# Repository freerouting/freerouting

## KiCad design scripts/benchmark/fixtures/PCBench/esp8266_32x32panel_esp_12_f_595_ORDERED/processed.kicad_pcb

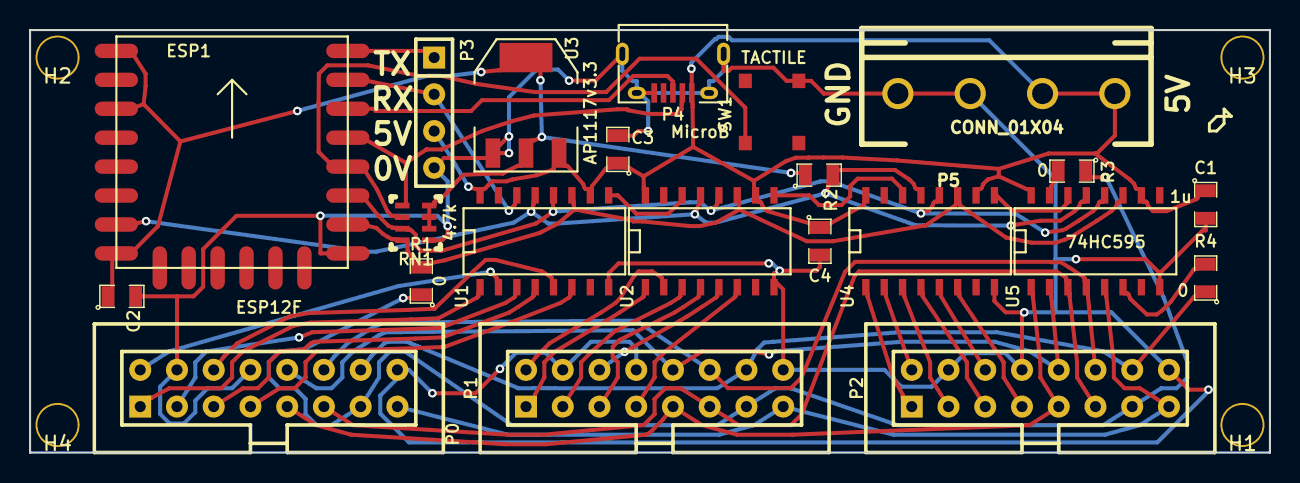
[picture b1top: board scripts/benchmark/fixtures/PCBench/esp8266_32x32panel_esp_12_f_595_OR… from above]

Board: 2 copper layers, 85.7 x 29.2 mm, 26 parts (0 on the bottom side), 41 nets.

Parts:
C1, C2, C3, C4: 1u; SM0805
ESP1: ESP12F; ESP12E
H1, H2, H3, H4: MH; SMTPIN
P0, P1, P2: RGB_OUT; RECT_20x2
P3: CONN_01X04; RECT_4x1
P4: MicroB; USBMicroB-10118194-0001LF
P5: CONN_01X04; PHOENIX1933202
R1, R3, R4: 0; SM0805
R2: 10k; SM0805
RN1: 4.7k; NETWORK1206
SW1: TACTILE
U1, U2, U4, U5: 74HC595; SO-16-N
U3: AP1117v3.3; SOT-223

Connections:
+3V3: C2.1, ESP1.1, ESP1.3, ESP1.8, R2.1, RN1.6, RN1.7, RN1.8, U3.2, U3.4
+5V: C1.1, C3.1, C4.1, P3.3, P4.1, P5.1, P5.2, U1.10, U1.16, U2.10, U2.16, U3.3, U4.10, U4.16, U5.10, U5.16
A: P0.9, P1.9, P2.9, U5.1
B: P0.10, P1.10, P2.10, U5.2
B0_0: P0.3, U1.3
B0_1: P1.3, U2.3
B0_2: P2.3, U4.3
B1_0: P0.7, U1.6
B1_1: P1.7, U2.6
B1_2: P2.7, U4.6
BCK: ESP1.16, R1.2, RN1.4, U1.11, U2.11, U4.11, U5.11
C: P0.11, P1.11, P2.11, U5.3
CLK: P0.13, P1.13, P2.13, R1.1, R3.1
D: P0.12, P1.12, P2.12, U5.4
D+: ESP1.20, P4.3
D-: ESP1.19, P4.2, RN1.1
ECLK: R3.2, U5.15
ESTB: R4.2, U5.6
G0_0: P0.2, U1.2
G0_1: P1.2, U2.2
G0_2: P2.2, U4.2
G1_0: P0.6, U1.5
G1_1: P1.6, U2.5
G1_2: P2.6, U4.5
GND: C1.2, C2.2, C3.2, C4.2, ESP1.15, P0.4, P0.8, P0.16, P1.4, P1.8, P1.16, P2.4, P2.8, P2.16, P3.4, P4.5, P4.6, P4.7, P4.8, P4.9, P5.3, P5.4, RN1.5, SW1.4, U1.8, U2.8, U3.1, U4.8, U5.8
GPIO0: ESP1.18, RN1.2, SW1.1
unnamed: ESP1.22, P3.1
unnamed: U1.9, U2.14
unnamed: U2.9, U4.14
unnamed: U4.9, U5.14
OE: P0.15, P1.15, P2.15, U5.5
OEX: ESP1.7, R2.2, U1.13, U2.13, U4.13, U5.13
R0_0: P0.1, U1.1
R0_1: P1.1, U2.1
R0_2: P2.1, U4.1
R1_0: P0.5, U1.4
R1_1: P1.5, U2.4
R1_2: P2.5, U4.4
SDI: ESP1.21, P3.2, U1.14
STB: P0.14, P1.14, P2.14, R4.1
WCK: ESP1.17, RN1.3, U1.12, U2.12, U4.12, U5.12

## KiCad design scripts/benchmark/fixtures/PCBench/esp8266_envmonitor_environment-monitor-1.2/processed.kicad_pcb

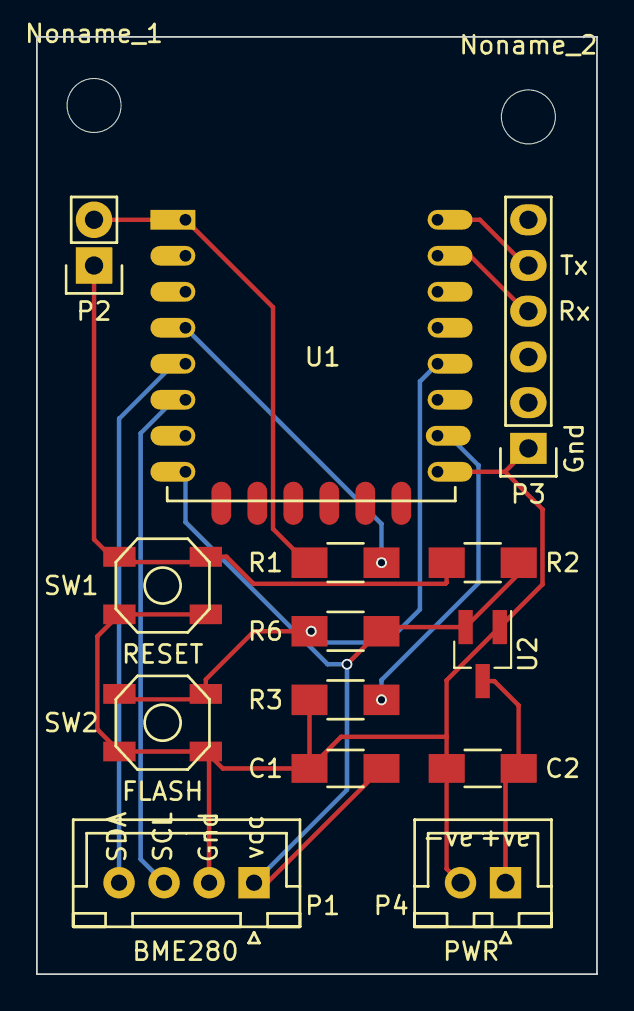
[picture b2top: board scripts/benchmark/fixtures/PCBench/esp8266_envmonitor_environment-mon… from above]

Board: 2 copper layers, 31.1 x 52.1 mm, 16 parts (0 on the bottom side), 12 nets.

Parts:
C1: 1uF; C_1206_HandSoldering
C2: 10uF; C_1206_HandSoldering
Noname_1, Noname_2: MountingHole_3mm
P1: BME280; JST_XH_B04B-XH-A_04x2.50mm_Straight
P2: HEADER; Pin_Header_Straight_1x02
P3: SERIAL; Pin_Header_Straight_1x06
P4: PWR; JST_XH_B02B-XH-A_02x2.50mm_Straight
R1: 10R; R_1206_HandSoldering
R2, R3, R6: 10k; R_1206_HandSoldering
SW1: RESET; SKQGAFE010_Switch
SW2: FLASH; SKQGAFE010_Switch
U1: ESP-12E
U2: MCP1700T-3302E/TT; SOT-23_Handsoldering

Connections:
/FLASH: R6.2, SW2.1, SW2.2, U1.18
/RXD: P3.4, U1.21
/SCL: P1.3, U1.6
/SDA: P1.4, U1.5
/TXD: P3.5, U1.22
GND: C1.2, C2.2, P1.2, P3.1, P4.2, R3.2, SW1.1, SW1.2, SW2.3, SW2.4, U1.15, U2.1
unnamed: C2.1, P4.1, U2.3
unnamed: P2.1, R2.2, SW1.3, SW1.4
unnamed: P2.2, R1.1, U1.1
unnamed: R1.2, U1.4
unnamed: R3.1, U1.16
VCC: C1.1, P1.1, R2.1, R6.1, U1.8, U2.2

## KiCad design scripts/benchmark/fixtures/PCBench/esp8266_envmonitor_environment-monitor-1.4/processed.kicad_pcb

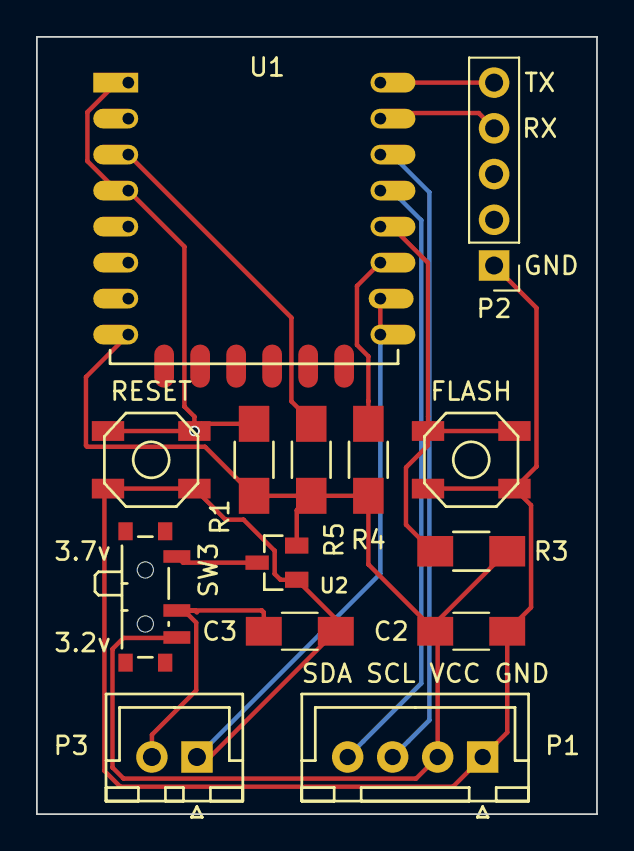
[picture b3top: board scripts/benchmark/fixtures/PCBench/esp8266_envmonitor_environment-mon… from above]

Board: 2 copper layers, 31.1 x 43.2 mm, 14 parts (0 on the bottom side), 12 nets.

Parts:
C2: 10uF; C_1206_HandSoldering
C3: 1uF; C_1206_HandSoldering
P1: BME280; JST_XH_B04B-XH-A_04x2.50mm_Straight
P2: SERIAL; Pin_Header_Straight_1x05_Pitch2.54mm
P3: PWR; JST_XH_B02B-XH-A_02x2.50mm_Straight
R1, R3, R4, R5: 4.7k; R_1206_HandSoldering
SW1: RESET; SKQGAFE010_Switch
SW2: FLASH; SKQGAFE010_Switch
SW3: Switch_SPDT_x2; SW_SPDT_PCM12
U1: ESP-12F; ESP-12E
U2: MCP1700T; SOT-23

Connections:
/CH_EN: R5.2, U1.3
/FLASH: R3.2, SW2.1, SW2.2, U1.18
/RXD: P2.4, U1.21
/SCL: P1.3, U1.20
/SDA: P1.4, U1.19
/TXD: P2.5, U1.22
GND: C2.2, C3.2, P1.1, P2.1, P3.1, SW1.1, SW1.2, SW2.3, SW2.4, U1.15, U1.16, U2.1
unnamed: C3.1, P3.2, SW3.2
unnamed: R1.2, SW1.3, SW1.4, U1.1, U1.4
unnamed: R4.2, U1.17
unnamed: SW3.1, U2.3
VCC: C2.1, P1.2, R1.1, R3.1, R4.1, R5.1, SW3.3, U1.8, U2.2

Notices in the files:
scripts/benchmark/fixtures/PCBench/esp8266_envmonitor_environment-monitor-1.2/processed.kicad_pcb:
Released under Solderpad Hardware License version 0.51
